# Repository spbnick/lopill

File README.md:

LoPill
=======

LoPill is a minimal development board for STM32L052C8T6 microcontroller, in
the form-factor of the popular "Blue Pill".

This work is licensed under a [Creative Commons Attribution-ShareAlike 4.0
International License](http://creativecommons.org/licenses/by-sa/4.0/).

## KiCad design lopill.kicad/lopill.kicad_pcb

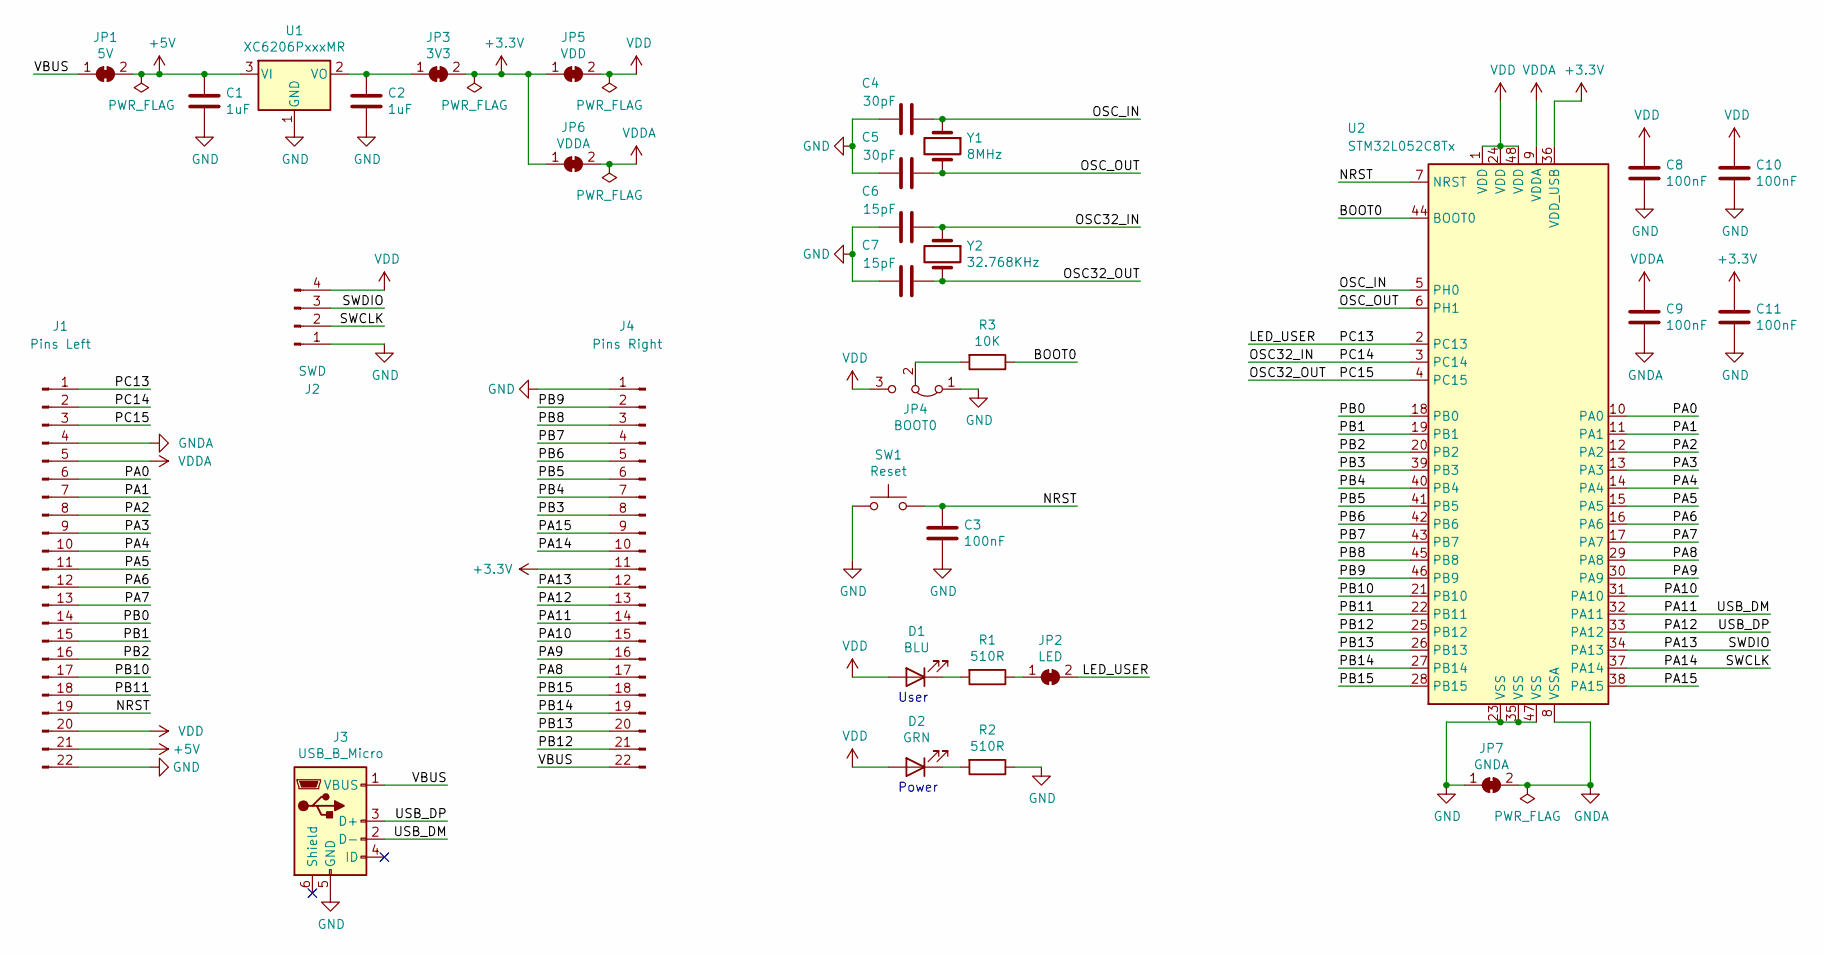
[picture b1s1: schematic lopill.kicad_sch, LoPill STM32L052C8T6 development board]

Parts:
C1, C2: 1uF; C_0402_1005Metric; LCSC C52923
C3, C8, C9, C10, C11: 100nF; C_0402_1005Metric; LCSC C1525
C4, C5: 30pF; C_0402_1005Metric; LCSC C159804
C6, C7: 15pF; C_0402_1005Metric; LCSC C1548
D1: BLU; LED_0603_1608Metric; LCSC C72041
D2: GRN; LED_0603_1608Metric; LCSC C72043
J1: Pins Left; PinHeader_1x22_P2.54mm_Vertical
J2: SWD; PinHeader_1x04_P2.54mm_Vertical
J3: USB_B_Micro; USB_Micro-B_HRO_U-D-M5DD-W-1_Vertical; LCSC C145795
J4: Pins Right; PinHeader_1x22_P2.54mm_Vertical
JP1: 5V; SolderJumper-2_P1.3mm_Bridged2Bar_RoundedPad1.0x1.5mm
JP2: LED; SolderJumper-2_P1.3mm_Bridged2Bar_RoundedPad1.0x1.5mm
JP3: 3V3; SolderJumper-2_P1.3mm_Bridged2Bar_RoundedPad1.0x1.5mm
JP4: BOOT0; PinHeader_1x03_P2.54mm_Vertical
JP5: VDD; SolderJumper-2_P1.3mm_Bridged2Bar_RoundedPad1.0x1.5mm
JP6: VDDA; SolderJumper-2_P1.3mm_Bridged2Bar_RoundedPad1.0x1.5mm
JP7: GNDA; SolderJumper-2_P1.3mm_Bridged2Bar_RoundedPad1.0x1.5mm
R1, R2: 510R; R_0402_1005Metric; LCSC C25123
R3: 10K; R_0402_1005Metric; LCSC C25744
SW1: Reset; SW_Push_1P1T_NO_5.1x5.1mm_H2.5mm; LCSC C318887
U1: XC6206PxxxMR; SOT-23; LCSC C5446
U2: STM32L052C8Tx; LQFP-48_7x7mm_P0.5mm; LCSC C111213
Y1: 8MHz; Crystal_SMD_5032-2Pin_5.0x3.2mm_YXC; LCSC C115962
Y2: 32.768KHz; Crystal_SMD_3215-2Pin_3.2x1.5mm; LCSC C32346

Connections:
+3V3: C11.1, J4.11, JP3.2 (B), JP5.1 (A), JP6.1 (A), U2.36 (VDD_USB)
+5V: C1.1, J1.21, JP1.2 (B), U1.3 (VI)
/BOOT0: R3.1, U2.44 (BOOT0)
/LED_USER: J1.1, JP2.2 (B), U2.2 (PC13)
/NRST: C3.1, J1.19, SW1.2, U2.7 (NRST)
/OSC32_IN: C6.1, J1.2, U2.3 (PC14), Y2.1
/OSC32_OUT: C7.1, J1.3, U2.4 (PC15), Y2.2
/OSC_IN: C4.1, U2.5 (PH0), Y1.1
/OSC_OUT: C5.1, U2.6 (PH1), Y1.2
/PA0: J1.6, U2.10 (PA0)
/PA1: J1.7, U2.11 (PA1)
/PA2: J1.8, U2.12 (PA2)
/PA3: J1.9, U2.13 (PA3)
/PA4: J1.10, U2.14 (PA4)
/PA5: J1.11, U2.15 (PA5)
/PA6: J1.12, U2.16 (PA6)
/PA7: J1.13, U2.17 (PA7)
/PA8: J4.17, U2.29 (PA8)
/PA9: J4.16, U2.30 (PA9)
/PA10: J4.15, U2.31 (PA10)
/PA11: J3.2 (D-), J4.14, U2.32 (PA11)
/PA12: J3.3 (D+), J4.13, U2.33 (PA12)
/PA13: J2.3, J4.12, U2.34 (PA13)
/PA14: J2.2, J4.10, U2.37 (PA14)
/PA15: J4.9, U2.38 (PA15)
/PB0: J1.14, U2.18 (PB0)
/PB1: J1.15, U2.19 (PB1)
/PB2: J1.16, U2.20 (PB2)
/PB3: J4.8, U2.39 (PB3)
/PB4: J4.7, U2.40 (PB4)
/PB5: J4.6, U2.41 (PB5)
/PB6: J4.5, U2.42 (PB6)
/PB7: J4.4, U2.43 (PB7)
/PB8: J4.3, U2.45 (PB8)
/PB9: J4.2, U2.46 (PB9)
/PB10: J1.17, U2.21 (PB10)
/PB11: J1.18, U2.22 (PB11)
/PB12: J4.21, U2.25 (PB12)
/PB13: J4.20, U2.26 (PB13)
/PB14: J4.19, U2.27 (PB14)
/PB15: J4.18, U2.28 (PB15)
/VBUS: J3.1 (VBUS), J4.22, JP1.1 (A)
GND: C1.2, C2.2, C3.2, C4.2, C5.2, C6.2, C7.2, C8.2, C10.2, C11.2, J1.22, J2.1, J3.5 (GND), J4.1, JP4.1 (A), JP7.1 (A), R2.1, SW1.1, U1.1 (GND), U2.23 (VSS), U2.35 (VSS), U2.47 (VSS)
GNDA: C9.2, J1.4, JP7.2 (B), U2.8 (VSSA)
unnamed: C2.1, JP3.1 (A), U1.2 (VO)
unnamed: D1.1 (K), R1.2
unnamed: D2.1 (K), R2.2
unnamed: JP2.1 (A), R1.1
unnamed: JP4.2 (C), R3.2
VDD: C8.1, C10.1, D1.2 (A), D2.2 (A), J1.20, J2.4, JP4.3 (B), JP5.2 (B), U2.1 (VDD), U2.24 (VDD), U2.48 (VDD)
VDDA: C9.1, J1.5, JP6.2 (B), U2.9 (VDDA)

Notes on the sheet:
Power
User

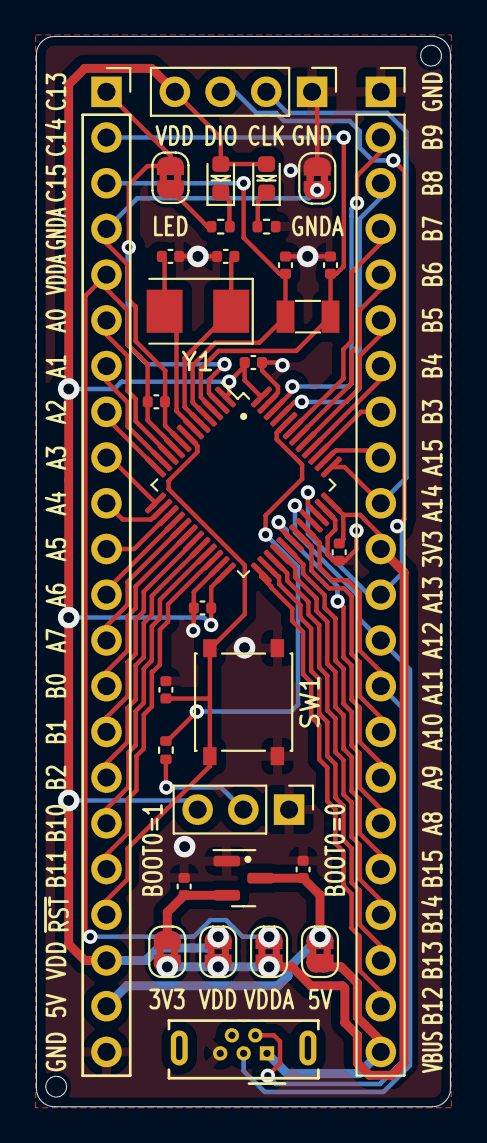
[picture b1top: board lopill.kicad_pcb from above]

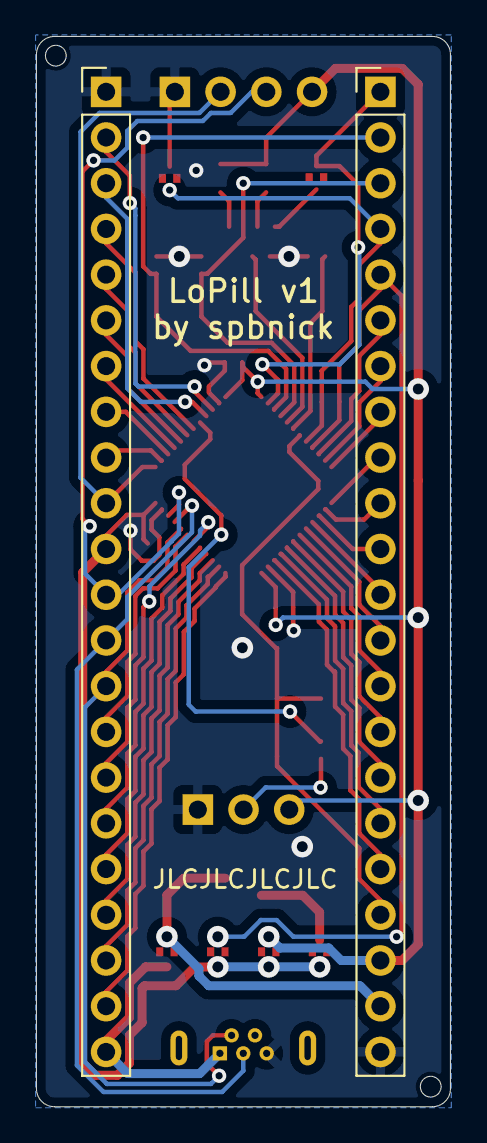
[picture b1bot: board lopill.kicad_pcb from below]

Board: 2 copper layers, 23.0 x 59.5 mm, 32 parts (2 on the bottom side), 51 nets.

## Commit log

2020-07-30 Add review-ready board
2020-07-31 Add 3D model of 8MHz crystal
2020-07-31 README.md: Add license note
2020-07-31 Lighten attribution text on back silkscreen
2020-07-31 Add JLCJLCJLCJLC placeholder
2020-08-01 Make lower jumper names appear on gerbers
2020-08-01 Make upper jumper names appear on gerbers
2020-09-26 Add notes.txt
2020-09-26 Add TODO.txt
2020-09-26 Add minimal firmware examples directory
2020-10-03 Switch to using the new rcc.h
2020-10-03 Use the new gpio.h
2020-10-03 Use constants everywhere
2020-10-03 Use libstammer init to get faster clock
2020-10-03 Add .gitignore to firmware examples
2020-10-03 Rename raw_blink.c to blink.c as it is cooked now
2020-10-11 TODO: Mention disconnecting USB shield
2020-10-11 Add I2C example code
2020-10-11 Lower I2C display brightness to avoid overheating
2020-10-12 Add touch sense controller usage example
2020-10-13 Expand TSC example to two sensor channels
2020-12-13 Explicitly initialize locals in tsc.c
2020-12-13 Be more careful about GPIO setup in blink.c
2020-12-13 Add usart.c
2020-12-13 Add KiCAD rescue library
2020-12-13 gitignore: Add a few more unneeded files
2020-12-13 usart: Fix alternate function assignment
2021-01-07 Switch blink.c to GPIO config functions
2022-05-14 Disconnect USB shield from ground
2022-05-14 Upgrade to KiCAD v6
2022-05-14 Move footprints to the shared library
